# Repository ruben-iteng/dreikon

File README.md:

<div align="center">

# DREIKON

</div>

## About

A triple button mechanical keyboard for all your macro needs.

## Features

- 3x hotswap sockets for Kailh low profile switches (CHOC v2)
- 3x RGB addressable LEDs for switch underglow
- 2x RGB addressable LEDs for front color bar
- USB Type-C
- 2x DIP switches for configuration
- RP2040 microcontroller

## Firmware

See the [firmware](./firmware/README.md) folder for info on setting up and using the firmware.

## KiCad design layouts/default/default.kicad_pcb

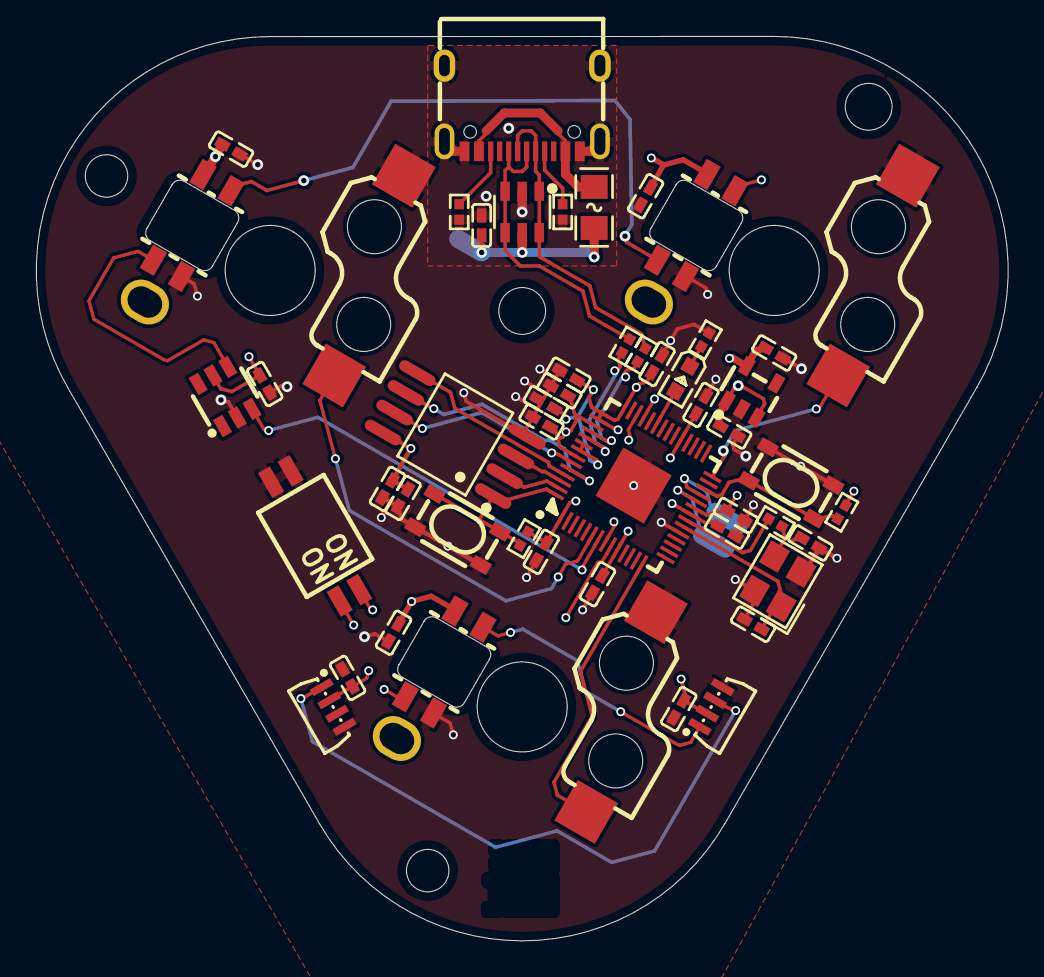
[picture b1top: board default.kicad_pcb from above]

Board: 4 copper layers, 54.0 x 50.2 mm, 52 parts (0 on the bottom side), 34 nets.

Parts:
C1, C2, C3, C5, C6, C10, C11, C12, C13, C14, C15, C17, C18, C19, C20, C21, C22, C23: 100nF ±10% 16V X7R; C0402
C4, C9, C16: 2.2µF ±20% 6.3V X5R; C0402
C7, C8: 15pF ±5% 50V C0G; C0402
D1: SOT-23-6_L2.9-W1.6-P0.95-LS2.8-BL
F1: F0805
LED1, LED2, LED3: LED-SMD_4P-L3.5-W3.5-P1.80-LS6.2_WS2812B-MINI-V3J
LED4: LED0603-RD
LED5, LED6: LED-SMD_WS2812B-4020
LOGO1: atopile_Logo_4x4mm
R1, R3, R4: 10kΩ ±1% 62.5mW; R0402
R2: 1kΩ ±1% 62.5mW; R0402
R5, R6: 27Ω ±1% 62.5mW; R0402
R7, R8: 5.1kΩ ±1% 62.5mW; R0402
SW1, SW2: KEY-SMD_4P-L4.2-W3.2-P2.20-LS4.6
SW3: SW-SMD_DSHP02TS-S
U1, U2, U3: CONN-SMD_HOTPLUGPAKAGE__C9900010116
U4: CRYSTAL-SMD_4P-L3.2-W2.5-BL
U5: LQFN-56_L7.0-W7.0-P0.4-EP
U6: SOIC-8_L5.3-W5.3-P1.27-LS8.0-BL
U7: SOT-23-5_L2.9-W1.6-P0.95-LS2.8-BR
U8: SOT-23-6_L2.9-W1.6-P0.95-LS2.8-BR
USB1: USB-C-SMD_TYPE-C-6PIN-2MD-073

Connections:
A: LED4.2, U5.37
GND: C1.2, C2.2, C3.2, C4.2, C5.2, C6.2, C7.2, C8.2, C9.2, C10.2, C11.2, C12.2, C13.2, C14.2, C15.2, C16.2, C17.2, C18.2, C19.2, C20.2, C21.2, C22.2, C23.2, D1.2, LED1.3, LED2.3, LED3.3, LED5.4, LED6.4, R3.1, R7.2, R8.2, SW1.3, SW1.4, SW2.3, SW2.4, SW3.3, SW3.4, U1.2, U2.2, U3.2, U4.2, U4.4, U5.19, U5.57, U6.4, U7.2, U8.2, USB1.1, USB1.12, USB1.13, USB1.14, USB1.15, USB1.16
K: LED4.1, R3.2
RUN: R4.1, SW2.1, SW2.2, U5.26
XIN: C7.1, U4.1, U5.20
XOUT: R2.2, U5.21
_core_regulator_out_power-VCC: C4.1, C5.1, C6.1, U5.23, U5.45, U5.50
cc[0]-line: R7.1, USB1.4
cc[1]-line: R8.1, USB1.10
chip_select: R1.1, SW1.1, SW1.2, U5.56, U6.1
clock: U5.52, U6.6
data_0: U5.53, U6.5
data_1: U5.55, U6.2
data_2: U5.54, U6.3
data_3: U5.51, U6.7
data_in-DIN: LED5.3, LED6.1
gpio[5]-line: U5.7, U8.3
gpio[6]-line: SW3.2, U5.8
gpio[7]-line: SW3.1, U5.9
input-USB_D_N: D1.1, D1.6, R6.1, USB1.5, USB1.7
input-USB_D_P: D1.3, D1.4, R5.1, USB1.6, USB1.8
led_data_out-DIN: LED3.2, LED5.1
led_power-VCC: C1.1, C2.1, C3.1, C18.1, C20.1, C21.1, C22.1, C23.1, D1.5, F1.2, LED1.1, LED2.1, LED3.1, LED5.2, LED6.2, U7.1, U7.3, U8.5
output: C8.1, R2.1, U4.3
output-USB_D_N: R6.2, U5.46
output-USB_D_P: R5.2, U5.47
power-VCC: C9.1, C10.1, C11.1, C12.1, C13.1, C14.1, C15.1, C16.1, C17.1, C19.1, R1.2, R4.2, U5.1, U5.10, U5.22, U5.33, U5.42, U5.43, U5.44, U5.48, U5.49, U6.8, U7.5
power_vbus-VCC: F1.1, USB1.2, USB1.11
switches[0]-led_data_in-line: LED1.4, U8.4
switches[0]-output-contact[0]: U1.1, U5.6
switches[1]-led_data_in-line: LED1.2, LED2.4
switches[1]-output-contact[0]: U2.1, U5.28
switches[2]-led_data_in-line: LED2.2, LED3.4
switches[2]-output-contact[0]: U3.1, U5.14

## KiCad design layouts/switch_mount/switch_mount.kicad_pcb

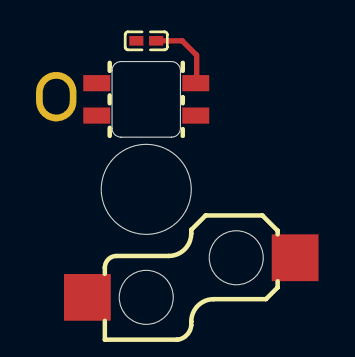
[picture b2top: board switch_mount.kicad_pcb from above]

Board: 2 copper layers, 3 parts (0 on the bottom side), 2 nets.

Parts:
C1: 100nF ±10% 16V X7R; C0402
LED1: LED-SMD_4P-L3.5-W3.5-P1.80-LS6.2_WS2812B-MINI-V3J
U2: CONN-SMD_HOTPLUGPAKAGE__C9900010116

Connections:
VCC: C1.1, LED1.1
power-GND: C1.2, LED1.3

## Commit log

2025-09-06 Add pull-up resistor to esp32-c3 boot pin
2025-09-12 Initial design and project files
2025-09-12 Add sub licence and build clean
2025-09-12 Remove publish workflow
2025-09-13 feat(PCB): Finish routing
2025-09-13 Fix CI hw build workflow
2025-09-13 Add 3D board render
2025-09-13 Fix CI build workflow
2025-09-13 Use latest logos package
2025-09-14 feat(fw): Minimal fw
